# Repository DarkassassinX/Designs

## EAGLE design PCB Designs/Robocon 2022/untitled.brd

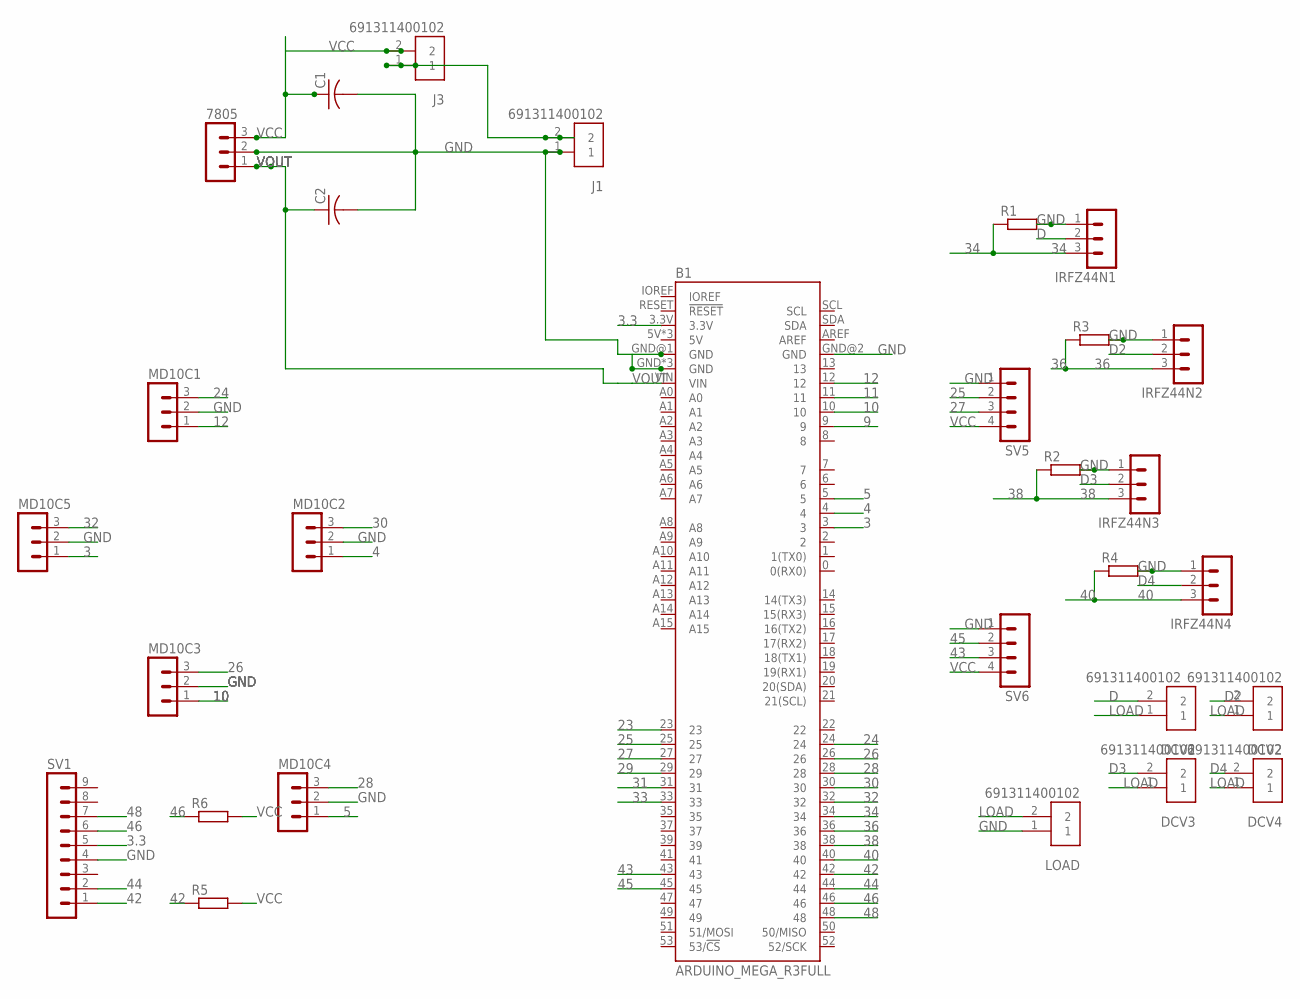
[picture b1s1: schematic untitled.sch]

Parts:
7805: MA03-1
B1: ARDUINO_MEGA_R3FULL; ARDUINO_MEGA_NO_SILK
C1, C2: C-US025-024X044; C025-024X044
DCV1, DCV2, DCV3, DCV4: 691311400102; TERMINALBLOCK_PLUGGABLE-2-7.62MM
IRFZ44N1, IRFZ44N2, IRFZ44N3, IRFZ44N4: MA03-1
J1, J3: 691311400102; TERMINALBLOCK_PLUGGABLE-2-7.62MM
LOAD: 691311400102; TERMINALBLOCK_PLUGGABLE-2-7.62MM
MD10C1, MD10C2, MD10C3, MD10C4, MD10C5: MA03-1
R1, R2, R3, R4, R5, R6: R-EU_0204_5; 0204/5
SV1: MA09-1
SV5, SV6: MA04-1

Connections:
3: B1.3, MD10C5.1
3.3: B1.3.3V, SV1.5
4: B1.4, MD10C2.1
5: B1.5, MD10C4.1
9: B1.9
10: B1.10, MD10C3.1
11: B1.11
12: B1.12, MD10C1.1
23: B1.23
24: B1.24, MD10C1.3
25: B1.25, SV5.2
26: B1.26, MD10C3.3
27: B1.27, SV5.3
28: B1.28, MD10C4.3
29: B1.29
30: B1.30, MD10C2.3
31: B1.31
32: B1.32, MD10C5.3
33: B1.33
34: B1.34, IRFZ44N1.3, R1.1
36: B1.36, IRFZ44N2.3, R3.1
38: B1.38, IRFZ44N3.3, R2.1
40: B1.40, IRFZ44N4.3, R4.1
42: B1.42, R5.1, SV1.1
43: B1.43, SV6.3
44: B1.44, SV1.2
45: B1.45, SV6.2
46: B1.46, R6.1, SV1.6
48: B1.48, SV1.7
D: DCV1.2, IRFZ44N1.2
D2: DCV2.2, IRFZ44N2.2
D3: DCV3.2, IRFZ44N3.2
D4: DCV4.2, IRFZ44N4.2
GND: 7805.2, B1.GND, B1.GND@1 (GND), B1.GND@2 (GND), B1.GND@3 (GND), B1.GND@4 (GND), C1.2, C2.2, IRFZ44N1.1, IRFZ44N2.1, IRFZ44N3.1, IRFZ44N4.1, J1.1, LOAD.1, MD10C1.2, MD10C2.2, MD10C3.2, MD10C4.2, MD10C5.2, R1.2, R2.2, R3.2, R4.2, SV1.4, SV5.1, SV6.1
LOAD: DCV1.1, DCV2.1, DCV3.1, DCV4.1, LOAD.2
VCC: 7805.3, C1.1, J3.2, R5.2, R6.2, SV5.4, SV6.4
VIN: J1.2, J3.1
VOUT: 7805.1, B1.VIN, C2.1

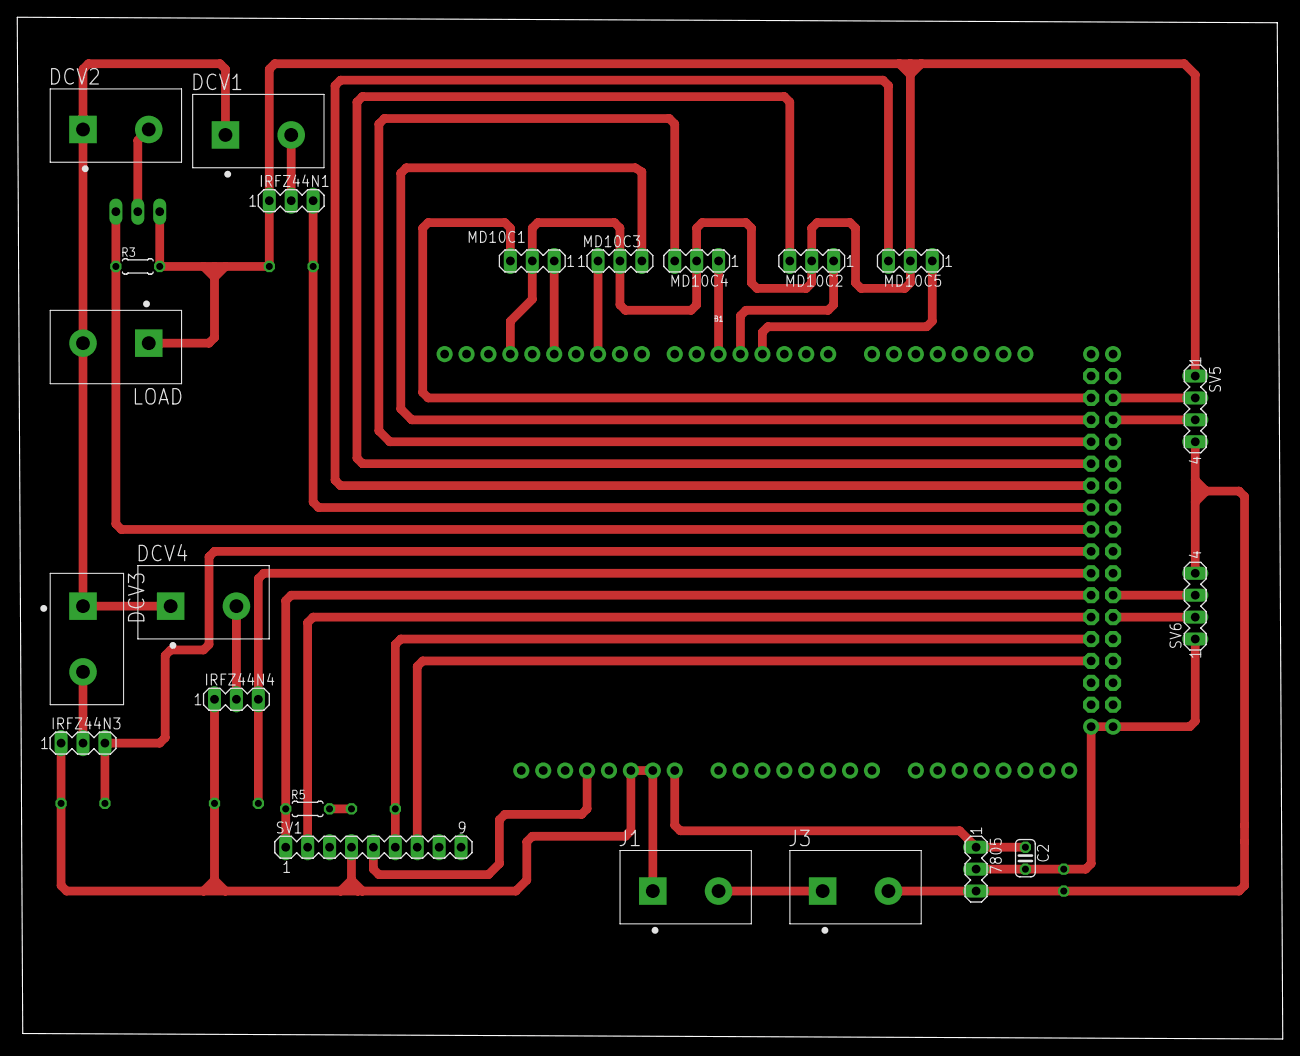
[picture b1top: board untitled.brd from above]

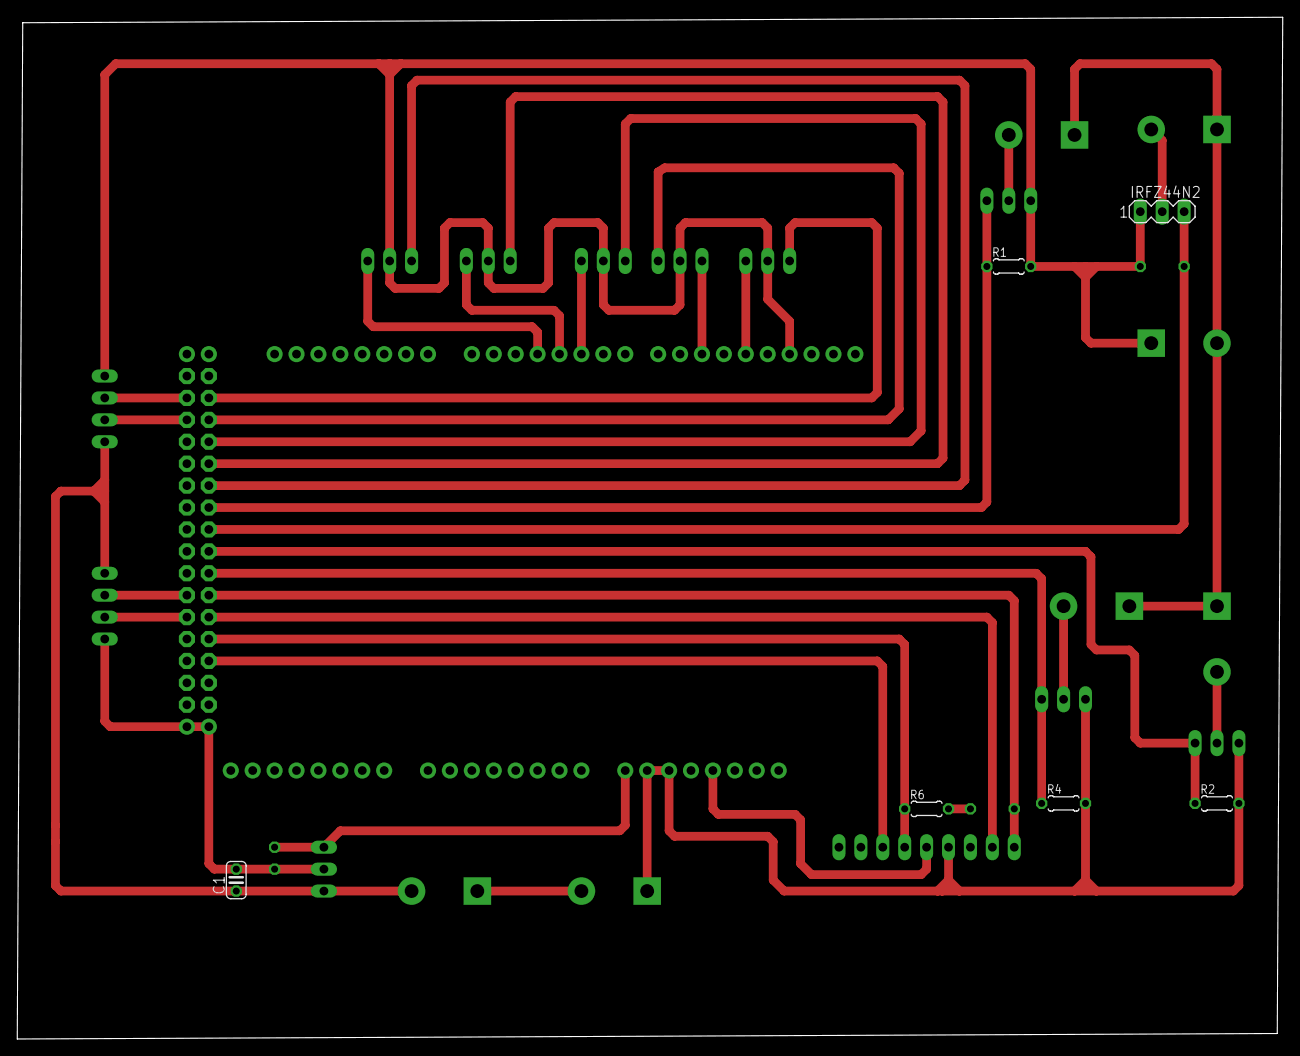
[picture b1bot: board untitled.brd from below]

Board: 2 copper layers, 146.7 x 118.4 mm, 29 parts (6 on the bottom side), 32 nets.

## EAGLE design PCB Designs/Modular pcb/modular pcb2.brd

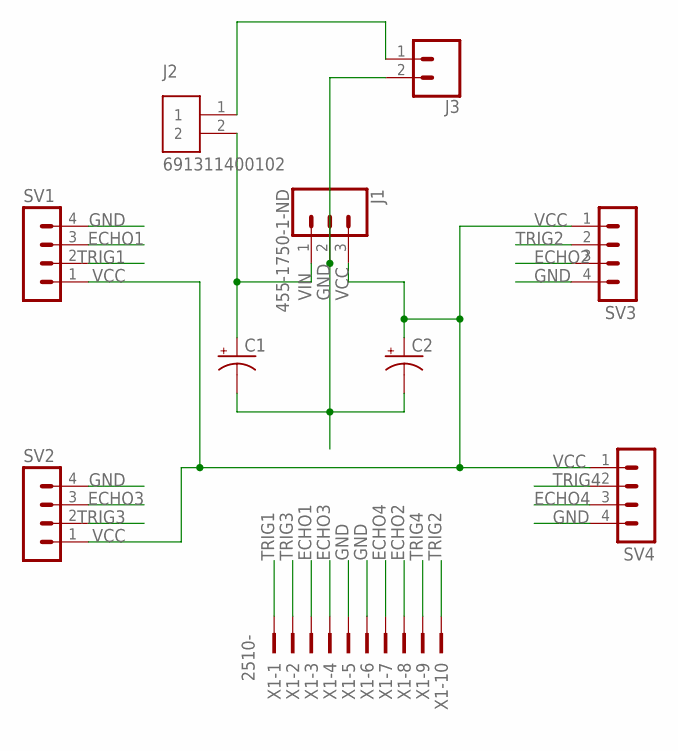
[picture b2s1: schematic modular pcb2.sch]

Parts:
C1, C2: 1F-2.7V(PTH)CPOL-RADIAL-1H-2.7V; CPOL-RADIAL-1F-2.7V
J1: 455-1750-1-ND; 1X03
J2: 691311400102; TERMINALBLOCK_PLUGGABLE-2-7.62MM
J3: CONN_02; 1X02
SV1, SV2, SV3, SV4: MA04-1
X1: 2510-; PAK100/2500-10

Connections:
ECHO1: SV1.3, X1.3
ECHO2: SV3.3, X1.8
ECHO3: SV2.3, X1.4
ECHO4: SV4.3, X1.7
GND: C1.-, C2.-, J1.2, J3.2, SV1.4, SV2.4, SV3.4, SV4.4, X1.5, X1.6
unnamed: J2.1, J3.1
TRIG1: SV1.2, X1.1
TRIG2: SV3.2, X1.10
TRIG3: SV2.2, X1.2
TRIG4: SV4.2, X1.9
VCC: C2.+, J1.3, SV1.1, SV2.1, SV3.1, SV4.1
VIN: C1.+, J1.1, J2.2

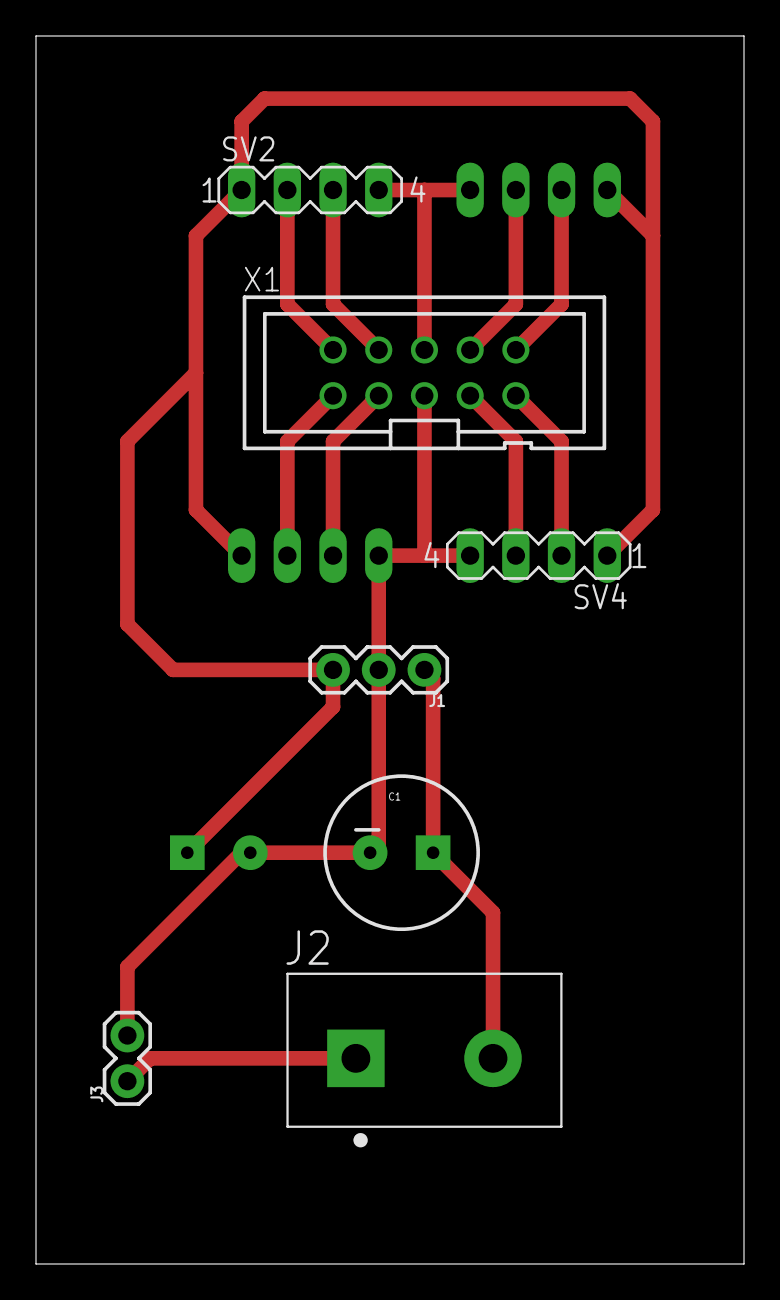
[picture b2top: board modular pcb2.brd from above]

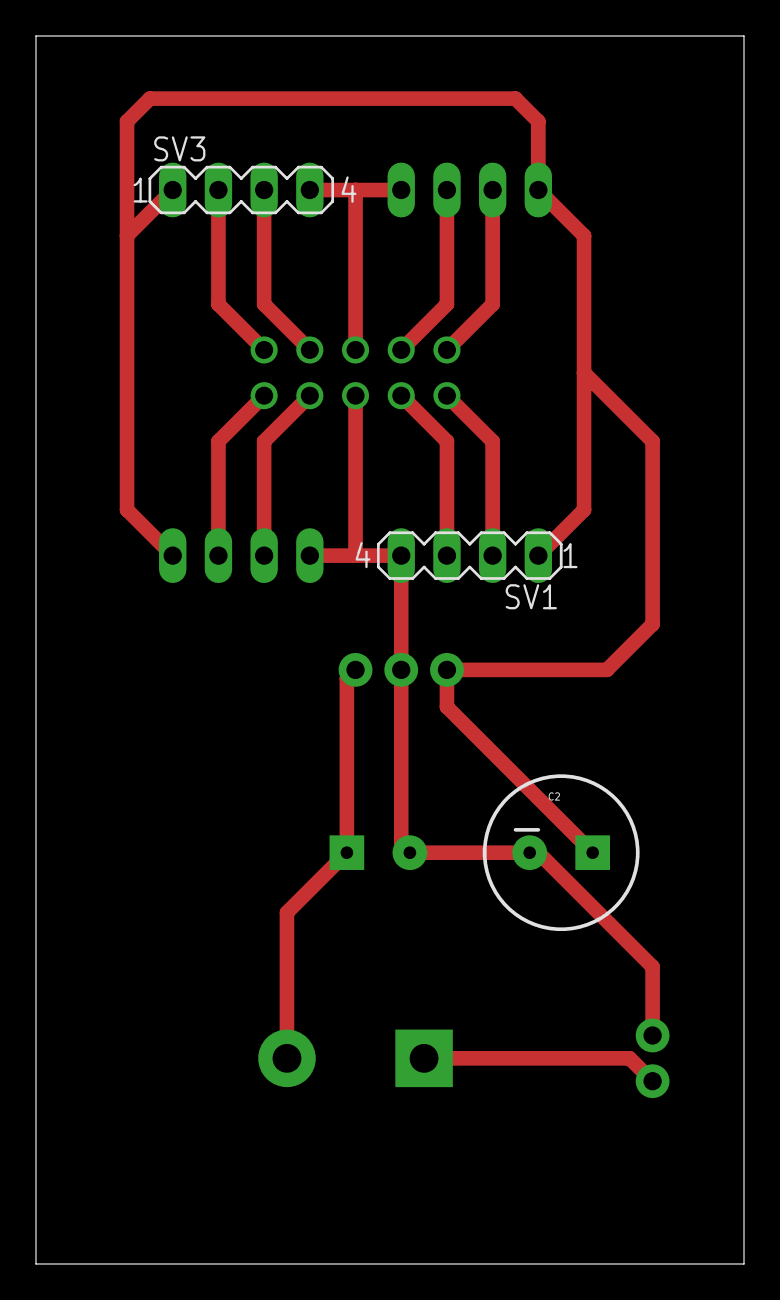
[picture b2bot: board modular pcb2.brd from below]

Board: 2 copper layers, 39.4 x 68.2 mm, 10 parts (3 on the bottom side), 12 nets.

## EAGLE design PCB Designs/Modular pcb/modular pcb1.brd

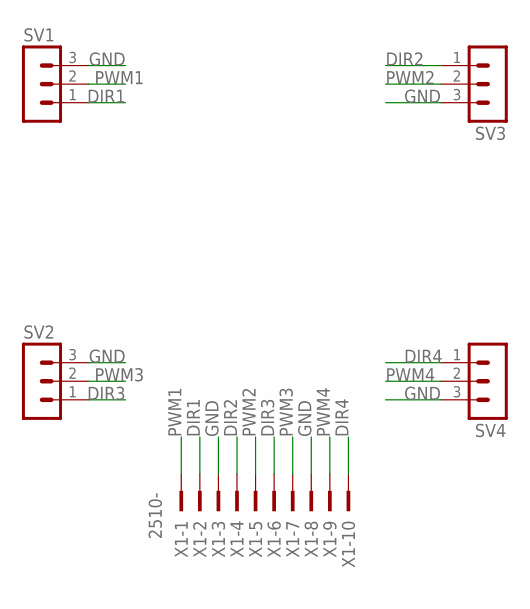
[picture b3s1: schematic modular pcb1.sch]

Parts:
SV1, SV2, SV3, SV4: MA03-1
X1: 2510-; PAK100/2500-10

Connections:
DIR1: SV1.1, X1.2
DIR2: SV3.1, X1.4
DIR3: SV2.1, X1.6
DIR4: SV4.1, X1.10
GND: SV1.3, SV2.3, SV3.3, SV4.3, X1.3, X1.8
PWM1: SV1.2, X1.1
PWM2: SV3.2, X1.5
PWM3: SV2.2, X1.7
PWM4: SV4.2, X1.9

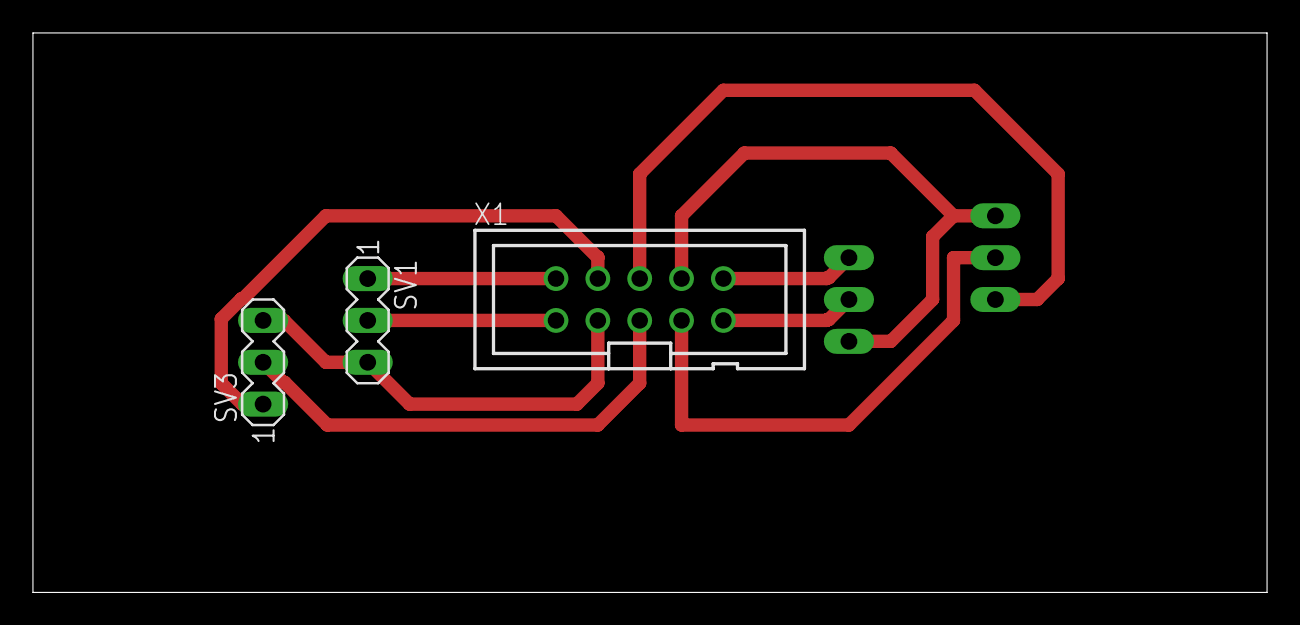
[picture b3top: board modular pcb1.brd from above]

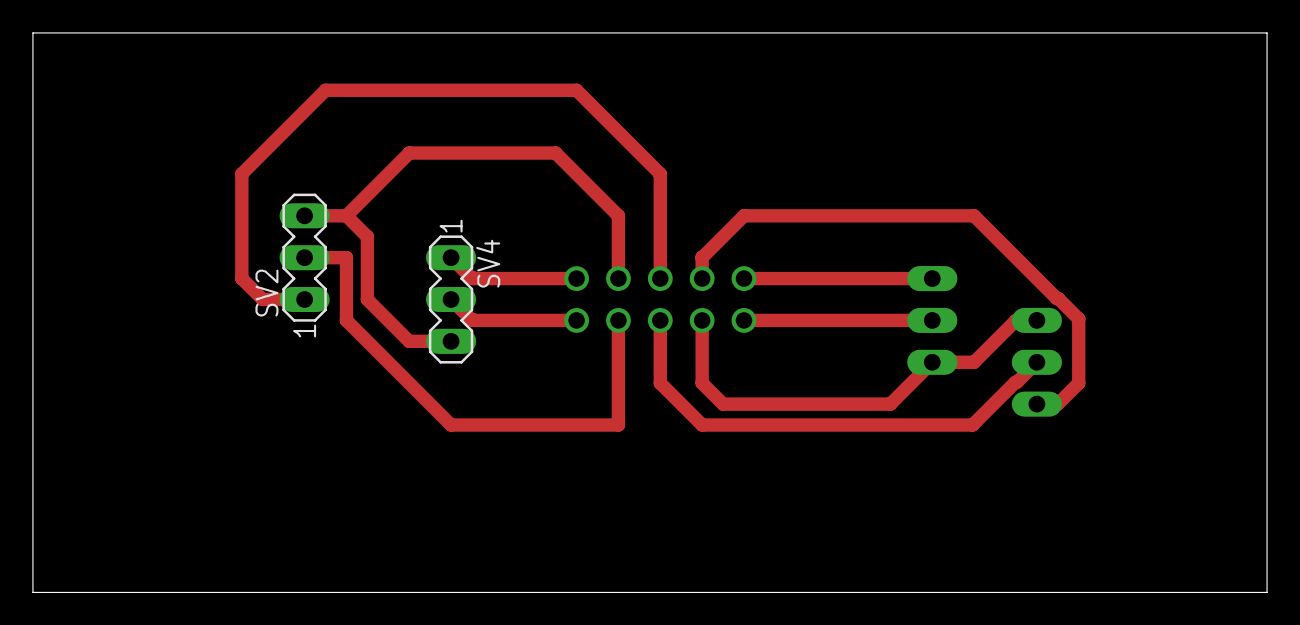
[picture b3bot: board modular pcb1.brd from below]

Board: 2 copper layers, 74.9 x 34.0 mm, 5 parts (2 on the bottom side), 9 nets.

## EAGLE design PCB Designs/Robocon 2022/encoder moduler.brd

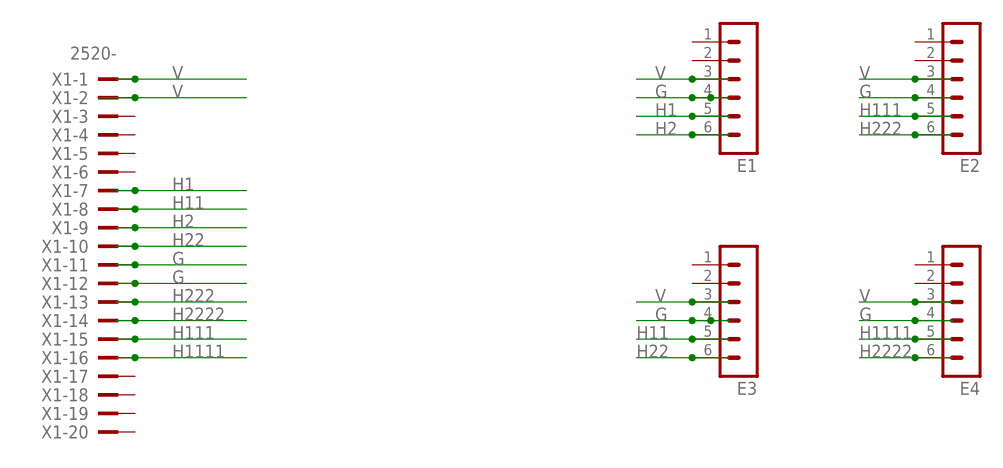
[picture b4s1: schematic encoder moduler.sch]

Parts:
E1, E2, E3, E4: MA06-1
X1: 2520-; PAK100/2500-20

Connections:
G: E1.4, E2.4, E3.4, E4.4, X1.11, X1.12
H1: E1.5, X1.7
H2: E1.6, X1.9
H11: E3.5, X1.8
H22: E3.6, X1.10
H111: E2.5, X1.15
H222: E2.6, X1.13
H1111: E4.5, X1.16
H2222: E4.6, X1.14
V: E1.3, E2.3, E3.3, E4.3, X1.1, X1.2

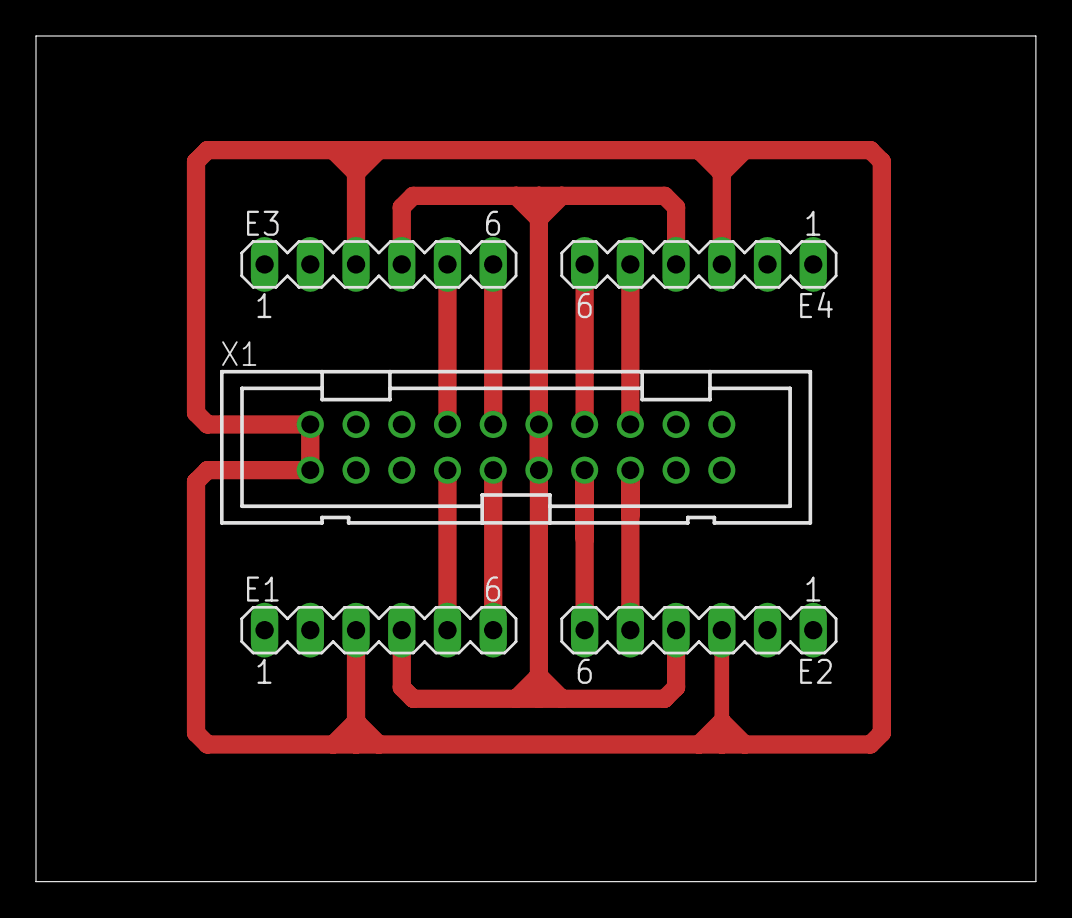
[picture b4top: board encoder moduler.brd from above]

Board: 2 copper layers, 55.6 x 47.0 mm, 5 parts (0 on the bottom side), 10 nets.

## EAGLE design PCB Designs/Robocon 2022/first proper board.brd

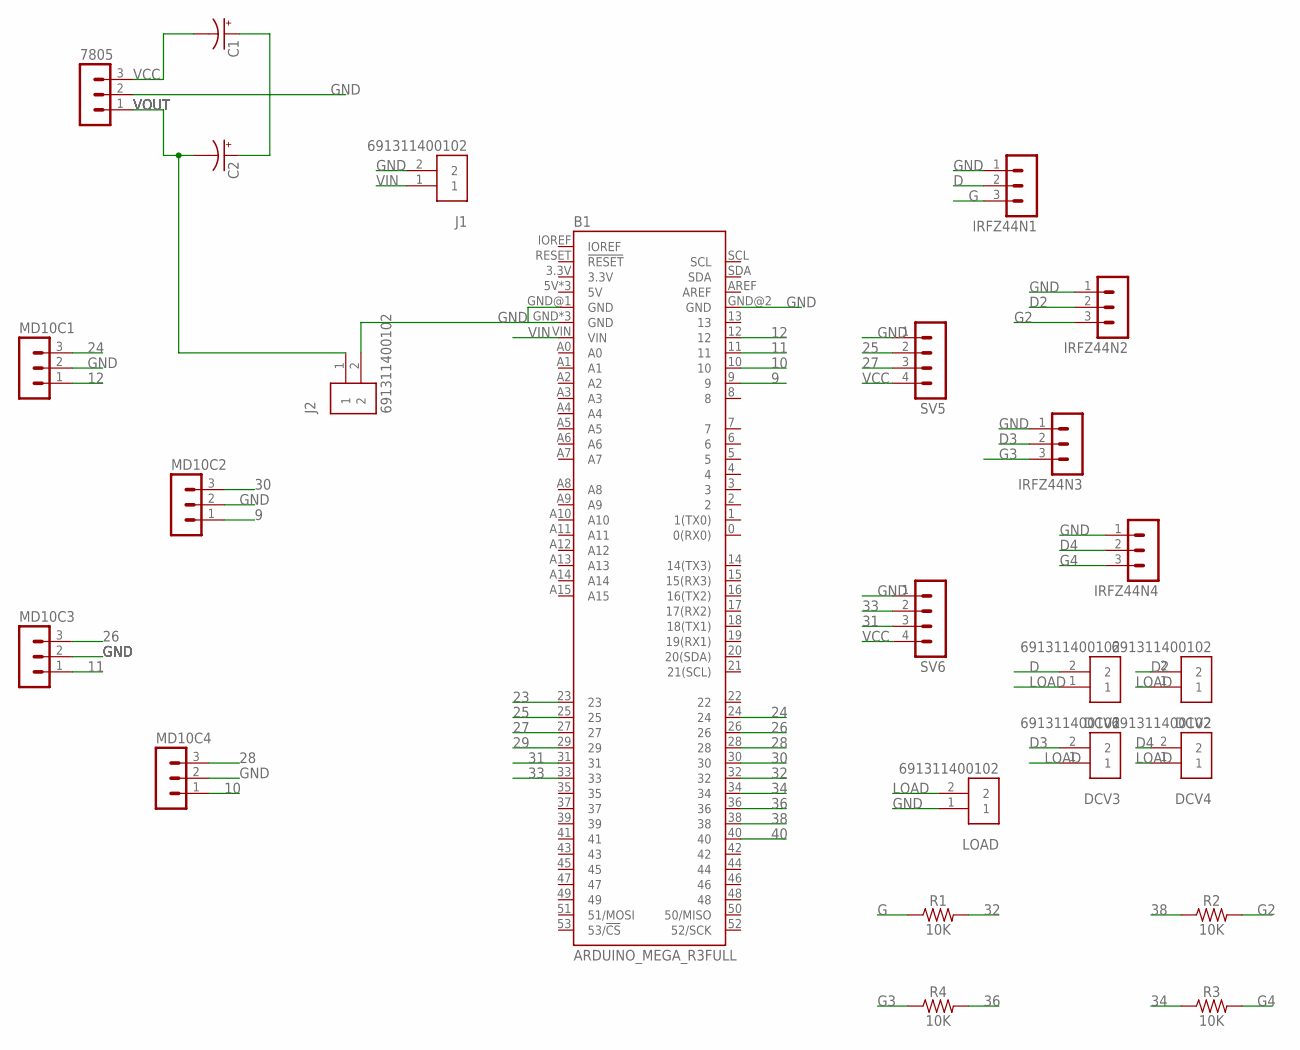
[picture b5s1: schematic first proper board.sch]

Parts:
7805: MA03-1
B1: ARDUINO_MEGA_R3FULL; ARDUINO_MEGA_NO_SILK
C1, C2: 1F-2.7V(PTH)CPOL-RADIAL-1H-2.7V; CPOL-RADIAL-1F-2.7V
DCV1, DCV2, DCV3, DCV4: 691311400102; TERMINALBLOCK_PLUGGABLE-2-7.62MM
IRFZ44N1, IRFZ44N2, IRFZ44N3, IRFZ44N4: MA03-1
J1, J2: 691311400102; TERMINALBLOCK_PLUGGABLE-2-7.62MM
LOAD: 691311400102; TERMINALBLOCK_PLUGGABLE-2-7.62MM
MD10C1, MD10C2, MD10C3, MD10C4: MA03-1
R1, R2, R3, R4: 10K; 0402-TIGHT
SV5, SV6: MA04-1

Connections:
9: B1.9, MD10C2.1
10: B1.10, MD10C4.1
11: B1.11, MD10C3.1
12: B1.12, MD10C1.1
23: B1.23
24: B1.24, MD10C1.3
25: B1.25, SV5.2
26: B1.26, MD10C3.3
27: B1.27, SV5.3
28: B1.28, MD10C4.3
29: B1.29
30: B1.30, MD10C2.3
31: B1.31, SV6.3
32: B1.32, R1.2
33: B1.33, SV6.2
34: B1.34, R3.1
36: B1.36, R4.2
38: B1.38, R2.1
40: B1.40
D: DCV1.2, IRFZ44N1.2
D2: DCV2.2, IRFZ44N2.2
D3: DCV3.2, IRFZ44N3.2
D4: DCV4.2, IRFZ44N4.2
G: IRFZ44N1.3, R1.1
G2: IRFZ44N2.3, R2.2
G3: IRFZ44N3.3, R4.1
G4: IRFZ44N4.3, R3.2
GND: 7805.2, B1.GND, B1.GND@1 (GND), B1.GND@2 (GND), B1.GND@3 (GND), B1.GND@4 (GND), IRFZ44N1.1, IRFZ44N2.1, IRFZ44N3.1, IRFZ44N4.1, J1.2, J2.2, LOAD.1, MD10C1.2, MD10C2.2, MD10C3.2, MD10C4.2, SV5.1, SV6.1
LOAD: DCV1.1, DCV2.1, DCV3.1, DCV4.1, LOAD.2
unnamed: C1.+, C2.+
VCC: 7805.3, C1.-, SV5.4, SV6.4
VIN: B1.VIN, J1.1
VOUT: 7805.1, C2.-, J2.1

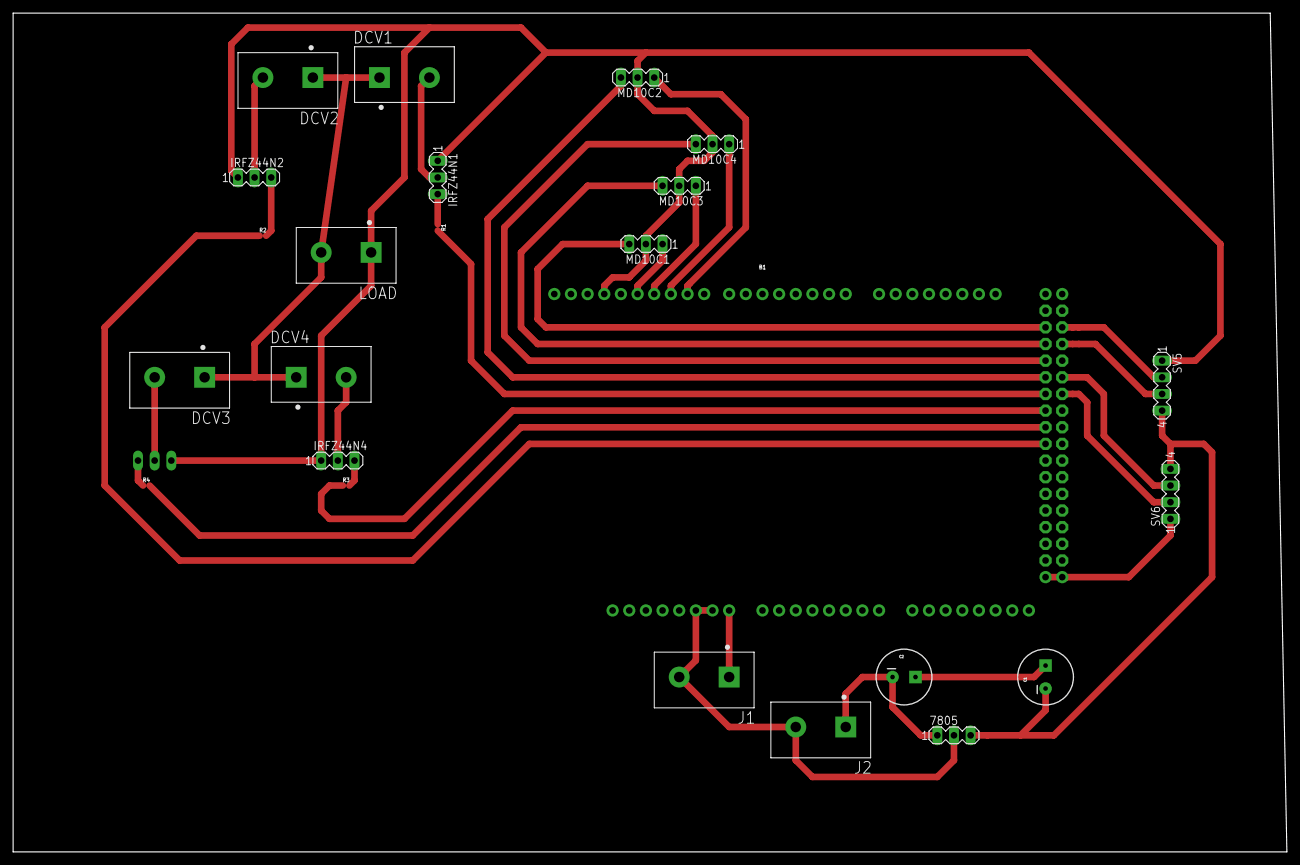
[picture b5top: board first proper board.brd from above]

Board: 2 copper layers, 194.3 x 127.9 mm, 25 parts (1 on the bottom side), 30 nets.

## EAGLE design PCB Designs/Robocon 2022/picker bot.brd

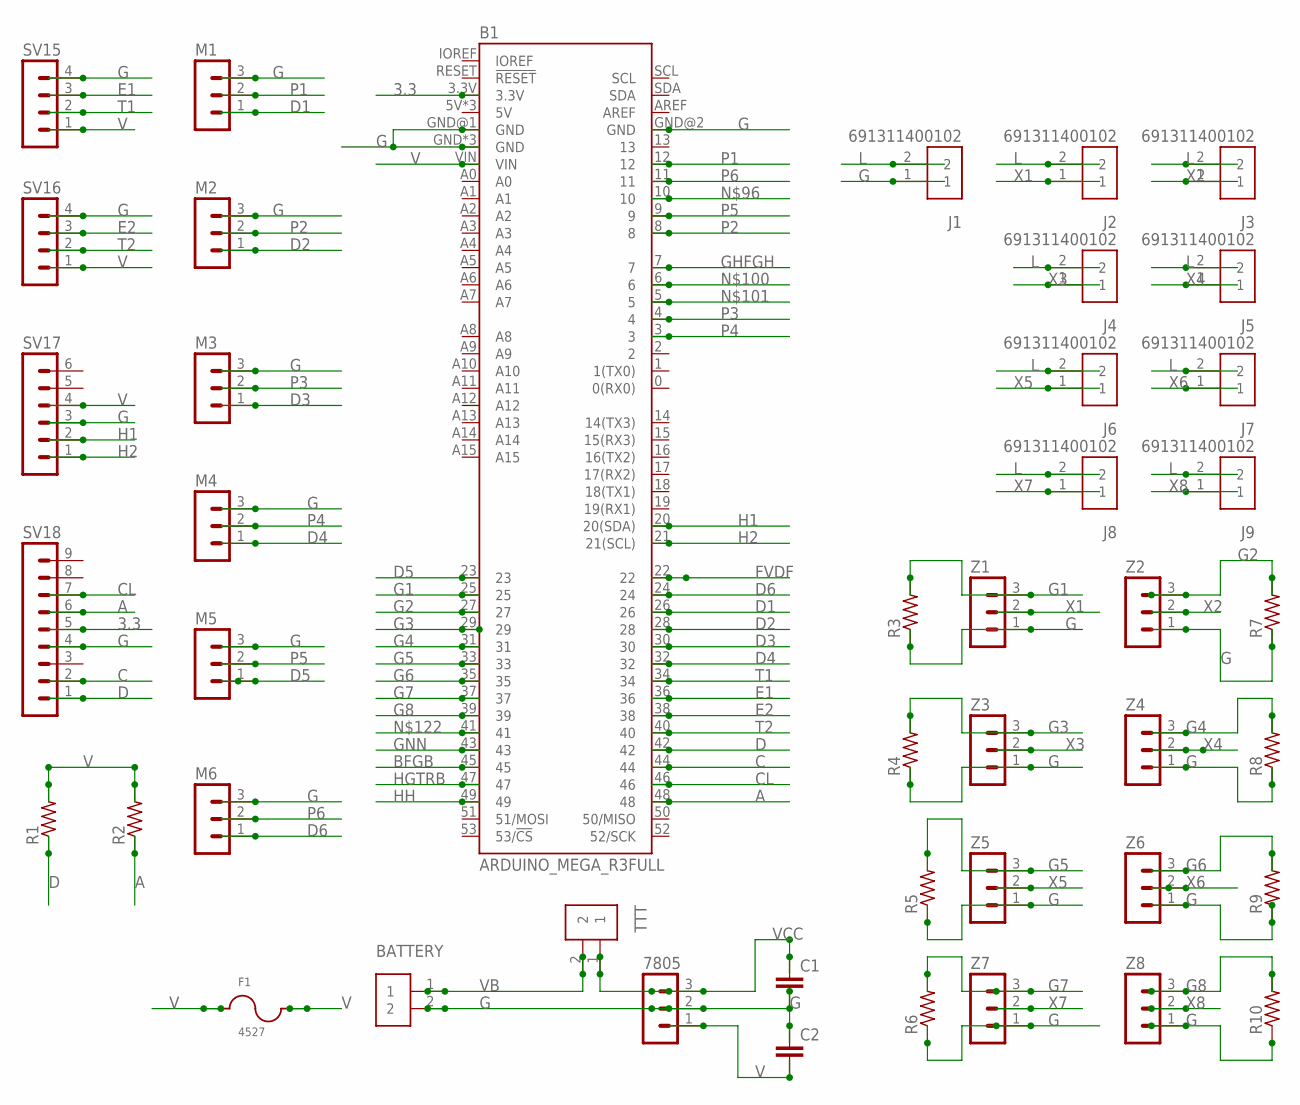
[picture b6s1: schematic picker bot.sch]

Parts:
7805: MA03-1
B1: ARDUINO_MEGA_R3FULL; ARDUINO_MEGA_NO_SILK
BATTERY: 691311400102; TERMINALBLOCK_PLUGGABLE-2-7.62MM
C1, C2: C-EU025-024X044; C025-024X044
F1: 4527
J1, J2, J3, J4, J5, J6, J7, J8, J9: 691311400102; TERMINALBLOCK_PLUGGABLE-2-7.62MM
M1, M2, M3, M4, M5, M6: MA03-1
R1, R2, R3, R4, R5, R6, R7, R8, R9, R10: R-US_0204/5; 0204/5
SV15, SV16: MA04-1
SV17: MA06-1
SV18: MA09-1
TTT: 691311400102; TERMINALBLOCK_PLUGGABLE-2-7.62MM
Z1, Z2, Z3, Z4, Z5, Z6, Z7, Z8: MA03-1

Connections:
3.3: B1.3.3V, SV18.5
A: B1.48, R2.1, SV18.6
BFGB: B1.45
C: B1.44, SV18.2
CL: B1.46, SV18.7
D: B1.42, R1.1, SV18.1
D1: B1.26, M1.1
D2: B1.28, M2.1
D3: B1.30, M3.1
D4: B1.32, M4.1
D5: B1.23, M5.1
D6: B1.24, M6.1
E1: B1.36, SV15.3
E2: B1.38, SV16.3
FVDF: B1.22
G: 7805.2, B1.GND, B1.GND@1 (GND), B1.GND@2 (GND), B1.GND@3 (GND), B1.GND@4 (GND), BATTERY.2, C1.2, C2.1, J1.1, M1.3, M2.3, M3.3, M4.3, M5.3, M6.3, R3.1, R4.1, R5.1, R6.1, R7.1, R8.1, R9.1, R10.1, SV15.4, SV16.4, SV17.3, SV18.4, Z1.1, Z2.1, Z3.1, Z4.1, Z5.1, Z6.1, Z7.1, Z8.1
G1: B1.25, R3.2, Z1.3
G2: B1.27, R7.2, Z2.3
G3: B1.29, R4.2, Z3.3
G4: B1.31, R8.2, Z4.3
G5: B1.33, R5.2, Z5.3
G6: B1.35, R9.2, Z6.3
G7: B1.37, R6.2, Z7.3
G8: B1.39, R10.2, Z8.3
GHFGH: B1.7
GNN: B1.43
H1: B1.20 (20(SDA)), SV17.2
H2: B1.21 (21(SCL)), SV17.1
HGTRB: B1.47
HH: B1.49
L: J1.2, J2.2, J3.2, J4.2, J5.2, J6.2, J7.2, J8.2, J9.2
P1: B1.12, M1.2
P2: B1.8, M2.2
P3: B1.4, M3.2
P4: B1.3, M4.2
P5: B1.9, M5.2
P6: B1.11, M6.2
T1: B1.34, SV15.2
T2: B1.40, SV16.2
V: 7805.1, B1.VIN, C2.2, F1.1, F1.2, R1.2, R2.2, SV15.1, SV16.1, SV17.4
VB: BATTERY.1, TTT.2
VCC: 7805.3, C1.1, TTT.1
X1: J2.1, Z1.2
X2: J3.1, Z2.2
X3: J4.1, Z3.2
X4: J5.1, Z4.2
X5: J6.1, Z5.2
X6: J7.1, Z6.2
X7: J8.1, Z7.2
X8: J9.1, Z8.2

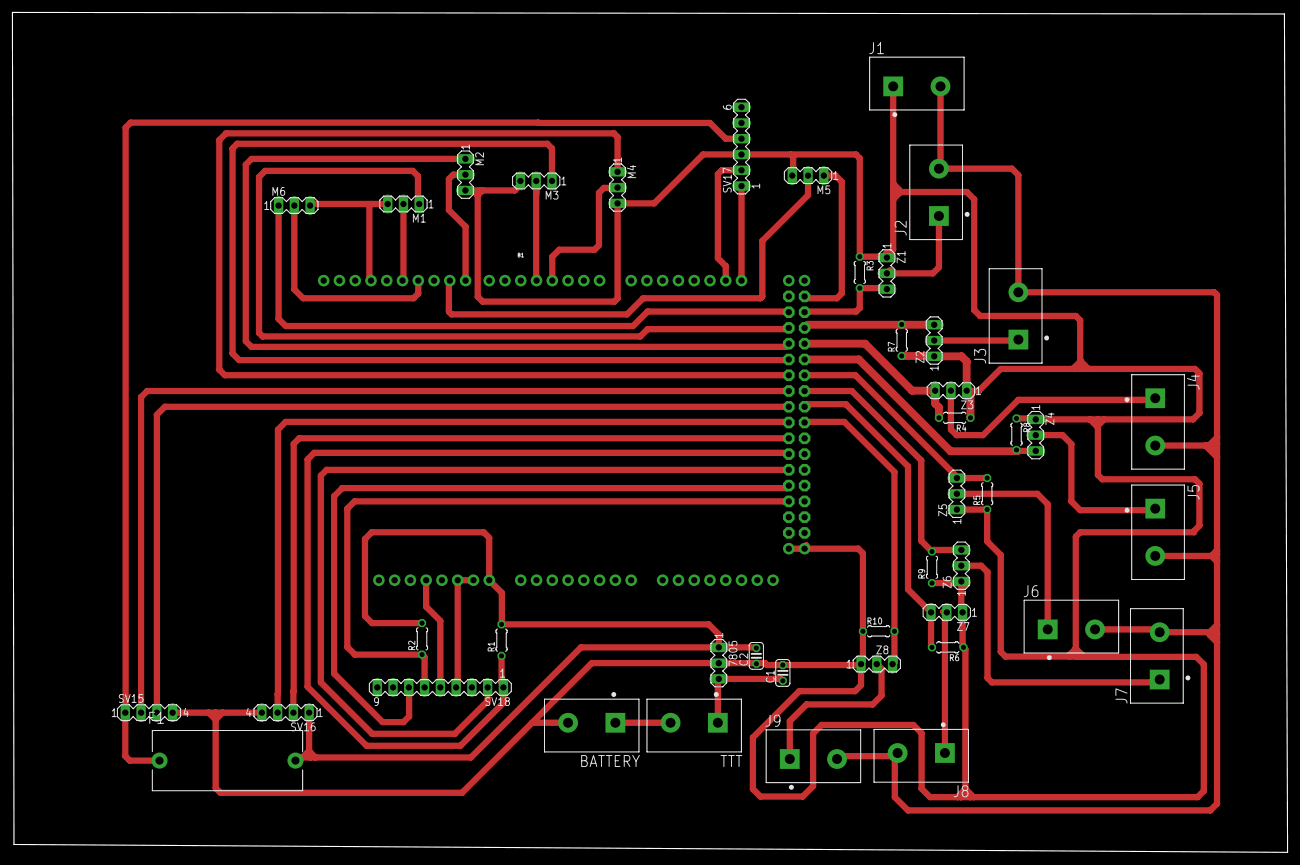
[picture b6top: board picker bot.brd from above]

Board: 2 copper layers, 205.4 x 135.3 mm, 44 parts (0 on the bottom side), 44 nets.

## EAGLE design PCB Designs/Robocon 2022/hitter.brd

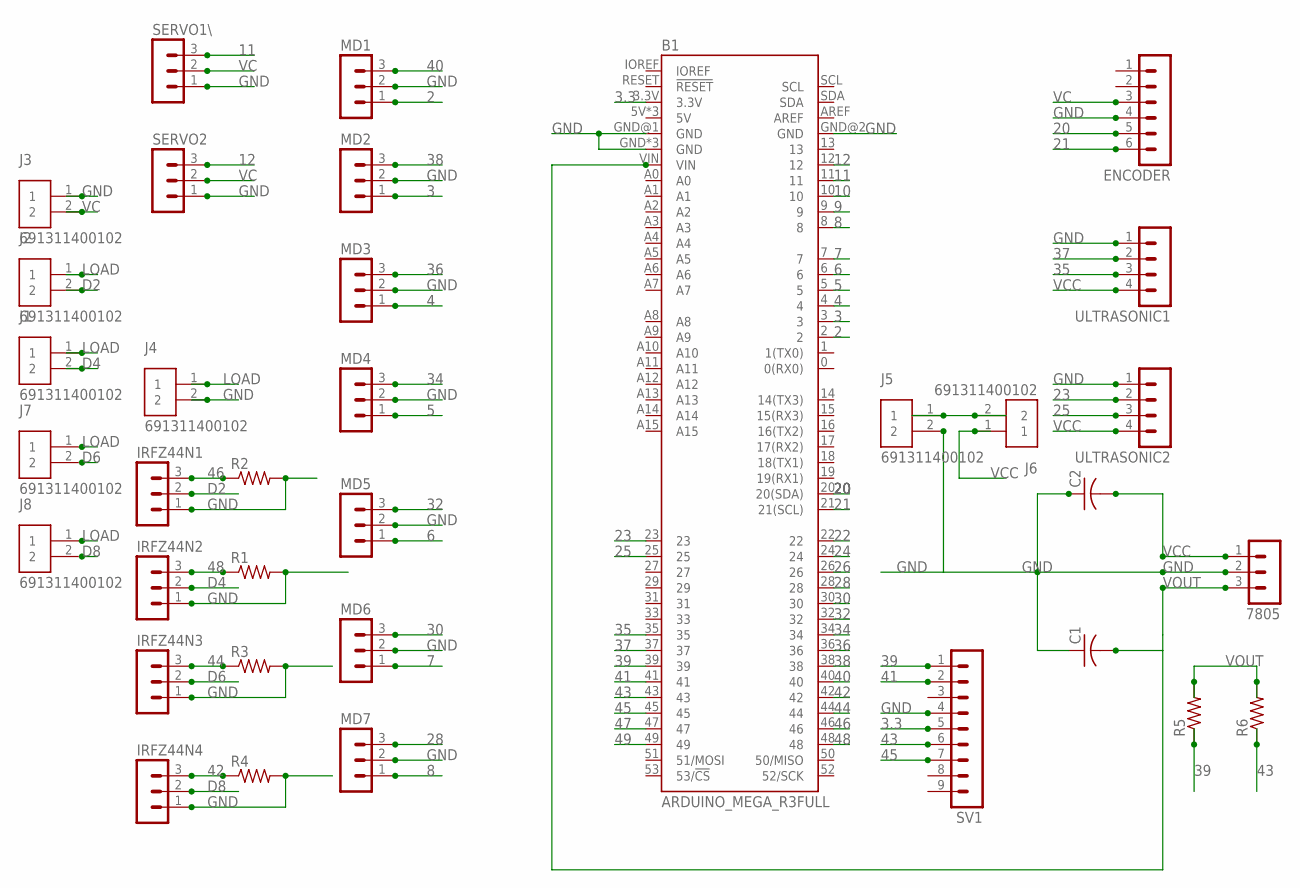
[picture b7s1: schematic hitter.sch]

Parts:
7805: MA03-1
B1: ARDUINO_MEGA_R3FULL; ARDUINO_MEGA_NO_SILK
C1, C2: C-US025-025X050; C025-025X050
ENCODER: MA06-1
IRFZ44N1, IRFZ44N2, IRFZ44N3, IRFZ44N4: MA03-1
J1, J2, J3, J4, J5, J6, J7, J8: 691311400102; TERMINALBLOCK_PLUGGABLE-2-7.62MM
MD1, MD2, MD3, MD4, MD5, MD6, MD7: MA03-1
R1, R2, R3, R4, R5, R6: R-US_0204/5; 0204/5
SERVO1\, SERVO2: MA03-1
SV1: MA09-1
ULTRASONIC1, ULTRASONIC2: MA04-1

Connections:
2: B1.2, MD1.1
3: B1.3, MD2.1
3.3: B1.3.3V, SV1.5
4: B1.4, MD3.1
5: B1.5, MD4.1
6: B1.6, MD5.1
7: B1.7, MD6.1
8: B1.8, MD7.1
9: B1.9
10: B1.10
11: B1.11, SERVO1\.3
12: B1.12, SERVO2.3
20: B1.20 (20(SDA)), ENCODER.5
21: B1.21 (21(SCL)), ENCODER.6
22: B1.22
23: B1.23, ULTRASONIC2.2
24: B1.24
25: B1.25, ULTRASONIC2.3
26: B1.26
28: B1.28, MD7.3
30: B1.30, MD6.3
32: B1.32, MD5.3
34: B1.34, MD4.3
35: B1.35, ULTRASONIC1.3
36: B1.36, MD3.3
37: B1.37, ULTRASONIC1.2
38: B1.38, MD2.3
39: B1.39, R5.1, SV1.1
40: B1.40, MD1.3
41: B1.41, SV1.2
42: B1.42, IRFZ44N4.3, R4.1
43: B1.43, R6.1, SV1.6
44: B1.44, IRFZ44N3.3, R3.1
45: B1.45, SV1.7
46: B1.46, IRFZ44N1.3, R2.1
47: B1.47
48: B1.48, IRFZ44N2.3, R1.1
49: B1.49
D2: IRFZ44N1.2, J2.2
D4: IRFZ44N2.2, J1.2
D6: IRFZ44N3.2, J7.2
D8: IRFZ44N4.2, J8.2
GND: 7805.2, B1.GND, B1.GND@1 (GND), B1.GND@2 (GND), B1.GND@3 (GND), B1.GND@4 (GND), C1.1, C2.1, ENCODER.4, IRFZ44N1.1, IRFZ44N2.1, IRFZ44N3.1, IRFZ44N4.1, J3.1, J4.2, J5.2, MD1.2, MD2.2, MD3.2, MD4.2, MD5.2, MD6.2, MD7.2, R1.2, R2.2, R3.2, R4.2, SERVO1\.1, SERVO2.1, SV1.4, ULTRASONIC1.1, ULTRASONIC2.1
LOAD: J1.1, J2.1, J4.1, J7.1, J8.1
unnamed: J5.1, J6.2
VC: ENCODER.3, J3.2, SERVO1\.2, SERVO2.2
VCC: 7805.1, C2.2, J6.1, ULTRASONIC1.4, ULTRASONIC2.4
VOUT: 7805.3, B1.VIN, C1.2, R5.2, R6.2

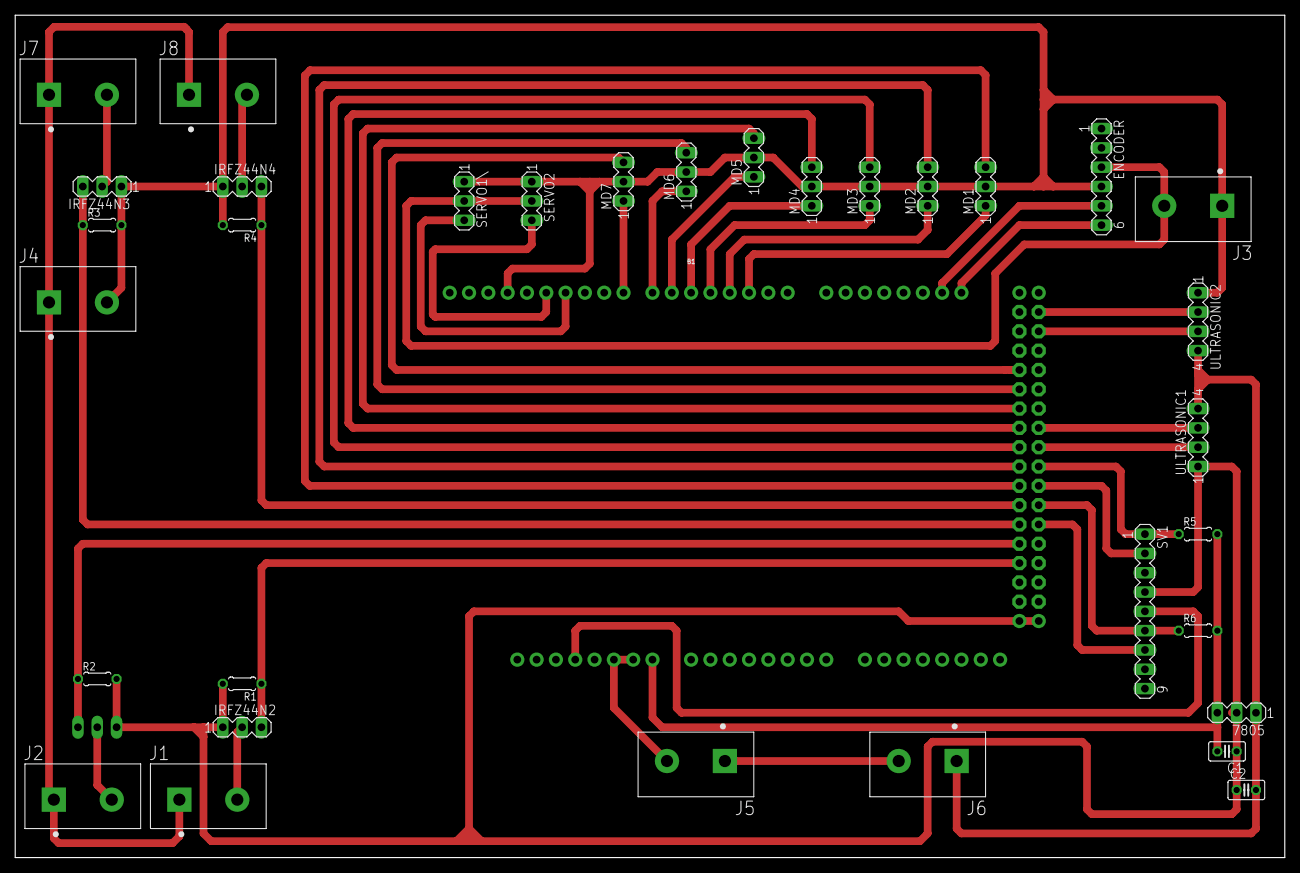
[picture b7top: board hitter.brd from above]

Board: 2 copper layers, 167.0 x 110.8 mm, 35 parts (1 on the bottom side), 41 nets.

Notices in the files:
parts and their libraries:
SparkFun-Connectors: Licensing: Creative Commons ShareAlike 4.0 International - https://creativecommons.org/licenses/by-sa/4.0
